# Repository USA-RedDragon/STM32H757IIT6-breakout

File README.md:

# STM32H757IIT6 Breakout

This board is aimed to evaluate the ST Microelectronics STM32H757IIT6 for use in an ultra-wideband SDR radio.

## Current Status

Not useful. This board should be usable for powering the STM, but features some unconnected pin headers.

## BOM

As of writing, the BOM comes out to $131.83 USD.

Octopart: https://octopart.com/bom-tool/58tXZVEL

## Size

TBD

## Images

All images below are of a pre-production board

### Top Right Angled View

### Top

## Bottom

## Usage

TODO

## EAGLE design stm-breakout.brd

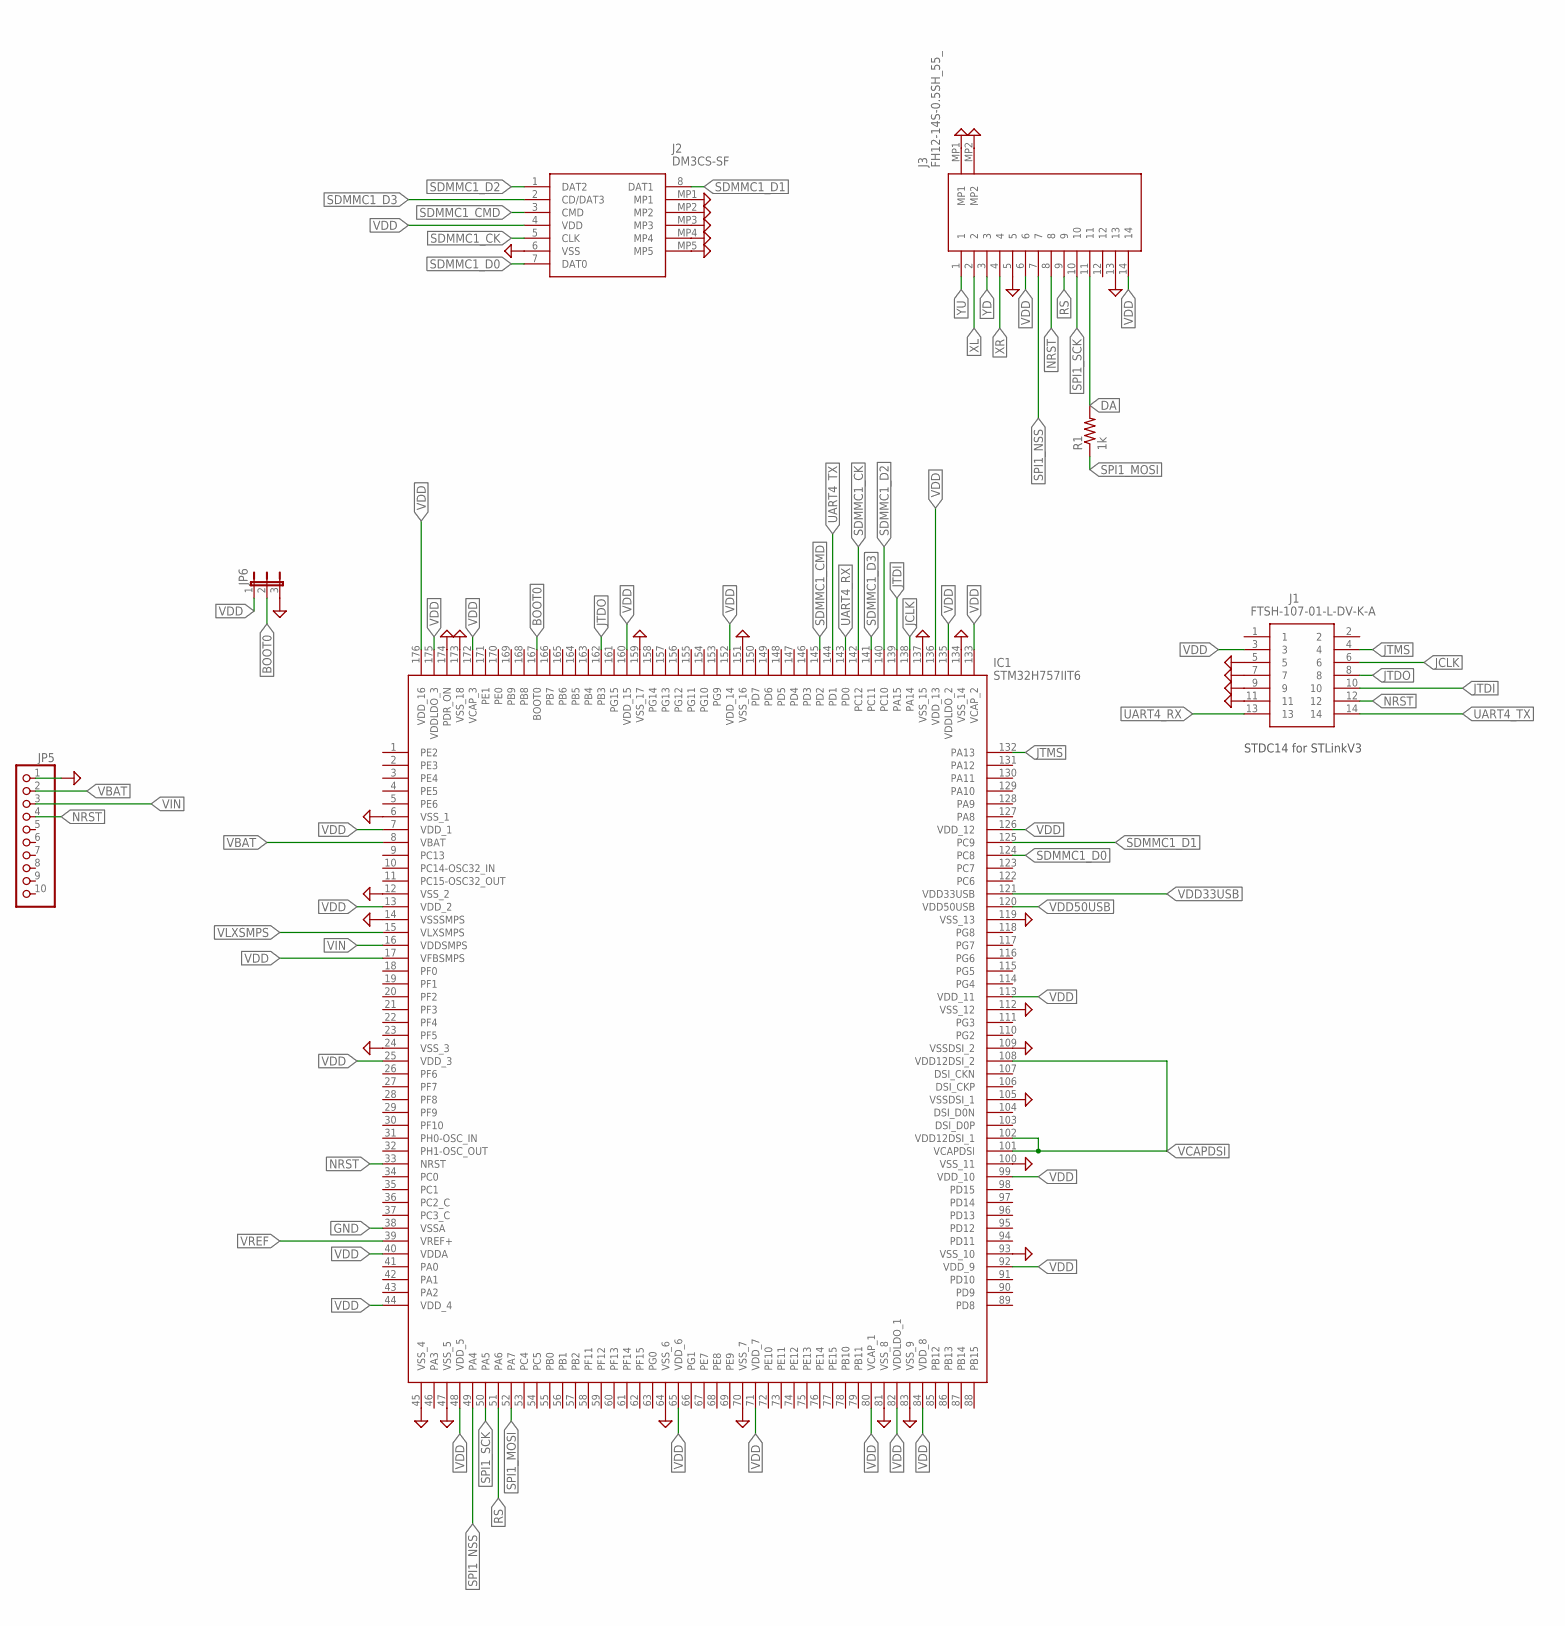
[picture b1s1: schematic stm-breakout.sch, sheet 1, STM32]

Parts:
IC1: STM32H757IIT6; QFP50P2600X2600X160-176N
J1: FTSH-107-01-L-DV-K-A; FTSH-107-XX-YYY-DV-K-A
J2: DM3CS-SF; DM3CSSF
J3: FH12-14S-0.5SH_55_; FH1214S05SH55
JP5: PINHD-1X10; 1X10
JP6: JP2
R1: 1k; R0402

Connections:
BOOT0: IC1.167 (BOOT0), JP6.2
DA: J3.11, R1.2
GND: IC1.6 (VSS_1), IC1.12 (VSS_2), IC1.14 (VSSSMPS), IC1.24 (VSS_3), IC1.38 (VSSA), IC1.45 (VSS_4), IC1.47 (VSS_5), IC1.64 (VSS_6), IC1.70 (VSS_7), IC1.81 (VSS_8), IC1.83 (VSS_9), IC1.93 (VSS_10), IC1.100 (VSS_11), IC1.105 (VSSDSI_1), IC1.109 (VSSDSI_2), IC1.112 (VSS_12), IC1.119 (VSS_13), IC1.134 (VSS_14), IC1.137 (VSS_15), IC1.151 (VSS_16), IC1.159 (VSS_17), IC1.173 (VSS_18), IC1.174 (PDR_ON), J1.5, J1.7, J1.9, J1.11, J2.6 (VSS), J2.MP1, J2.MP2, J2.MP3, J2.MP4, J2.MP5, J3.5, J3.13, J3.MP1, J3.MP2, JP5.1, JP6.3; also elsewhere on the board
JCLK: IC1.138 (PA14), J1.6
JTDI: IC1.139 (PA15), J1.10
JTDO: IC1.162 (PB3), J1.8
JTMS: IC1.132 (PA13), J1.4
NRST: IC1.33 (NRST), J1.12, J3.8, JP5.4; also elsewhere on the board
RS: IC1.51 (PA6), J3.9
SDMMC1_CK: IC1.142 (PC12), J2.5 (CLK)
SDMMC1_CMD: IC1.145 (PD2), J2.3 (CMD)
SDMMC1_D0: IC1.124 (PC8), J2.7 (DAT0)
SDMMC1_D1: IC1.125 (PC9), J2.8 (DAT1)
SDMMC1_D2: IC1.140 (PC10), J2.1 (DAT2)
SDMMC1_D3: IC1.141 (PC11), J2.2 (CD/DAT3)
SPI1_MOSI: IC1.52 (PA7), R1.1
SPI1_NSS: IC1.49 (PA4), J3.7
SPI1_SCK: IC1.50 (PA5), J3.10
UART4_RX: IC1.143 (PD0), J1.13
UART4_TX: IC1.144 (PD1), J1.14
VBAT: IC1.8 (VBAT), JP5.2
VCAPDSI: IC1.101 (VCAPDSI), IC1.102 (VDD12DSI_1), IC1.108 (VDD12DSI_2); also elsewhere on the board
VDD: IC1.7 (VDD_1), IC1.13 (VDD_2), IC1.17 (VFBSMPS), IC1.25 (VDD_3), IC1.40 (VDDA), IC1.44 (VDD_4), IC1.48 (VDD_5), IC1.65 (VDD_6), IC1.71 (VDD_7), IC1.80 (VCAP_1), IC1.82 (VDDLDO_1), IC1.84 (VDD_8), IC1.92 (VDD_9), IC1.99 (VDD_10), IC1.113 (VDD_11), IC1.126 (VDD_12), IC1.133 (VCAP_2), IC1.135 (VDDLDO_2), IC1.136 (VDD_13), IC1.152 (VDD_14), IC1.160 (VDD_15), IC1.172 (VCAP_3), IC1.175 (VDDLDO_3), IC1.176 (VDD_16), J1.3, J2.4 (VDD), J3.6, J3.14, JP6.1; also elsewhere on the board
VDD33USB: IC1.121 (VDD33USB); also elsewhere on the board
VDD50USB: IC1.120 (VDD50USB); also elsewhere on the board
VIN: IC1.16 (VDDSMPS), JP5.3; also elsewhere on the board
VLXSMPS: IC1.15 (VLXSMPS); also elsewhere on the board
VREF: IC1.39 (VREF+); also elsewhere on the board
XL: J3.2
XR: J3.4
YD: J3.3
YU: J3.1

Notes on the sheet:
STDC14 for STLinkV3

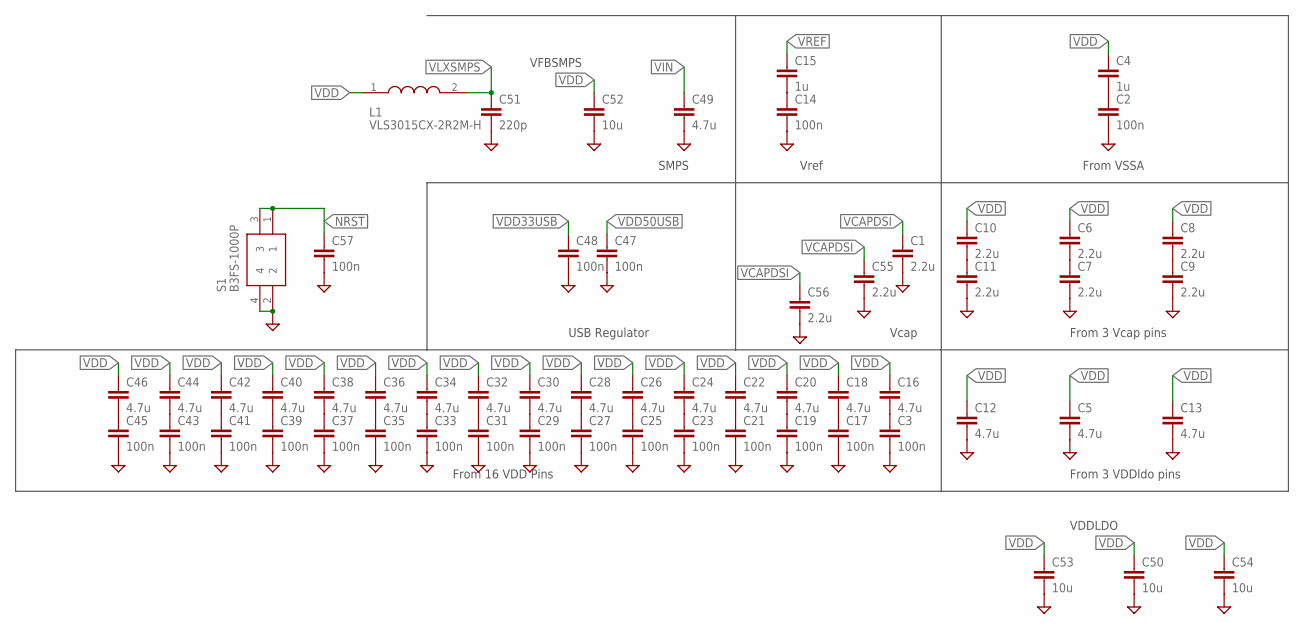
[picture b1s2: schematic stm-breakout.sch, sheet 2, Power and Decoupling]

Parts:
C1, C6, C7, C8, C9, C10, C11, C55, C56: 2.2u; C0603
C2, C3, C14, C17, C19, C21, C23, C25, C27, C29, C31, C33, C35, C37, C39, C41, C43, C45, C47, C48, C57: 100n; C0402
C4, C15: 1u; C0603
C5, C12, C13, C16, C18, C20, C22, C24, C26, C28, C30, C32, C34, C36, C38, C40, C42, C44, C46, C49: 4.7u; C0603
C50, C52, C53, C54: 10u; C0603
C51: 220p; C0402
L1: VLS3015CX-2R2M-H; VLS3015
S1: B3FS-1000P

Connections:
GND: C1.2, C2.2, C3.2, C5.2, C7.2, C9.2, C11.2, C12.2, C13.2, C14.2, C17.2, C19.2, C21.2, C23.2, C25.2, C27.2, C29.2, C31.2, C33.2, C35.2, C37.2, C39.2, C41.2, C43.2, C45.2, C47.2, C48.2, C49.2, C50.2, C51.2, C52.2, C53.2, C54.2, C55.2, C56.2, C57.2, S1.2, S1.4; also elsewhere on the board
unnamed: C2.1, C4.2
unnamed: C6.2, C7.1
unnamed: C8.2, C9.1
unnamed: C10.2, C11.1
NRST: C57.1, S1.1, S1.3; also elsewhere on the board
VCAPDSI: C1.1, C55.1, C56.1; also elsewhere on the board
VDD: C4.1, C5.1, C6.1, C8.1, C10.1, C12.1, C13.1, C16.1, C18.1, C20.1, C22.1, C24.1, C26.1, C28.1, C30.1, C32.1, C34.1, C36.1, C38.1, C40.1, C42.1, C44.1, C46.1, C50.1, C52.1, C53.1, C54.1, L1.1; also elsewhere on the board
VDD33USB: C48.1; also elsewhere on the board
VDD50USB: C47.1; also elsewhere on the board
VIN: C49.1; also elsewhere on the board
VLXSMPS: C51.1, L1.2; also elsewhere on the board
VREF: C15.1; also elsewhere on the board
VREFNF: C14.1, C15.2
VREFNF1: C3.1, C16.2
VREFNF2: C17.1, C18.2
VREFNF3: C19.1, C20.2
VREFNF4: C21.1, C22.2
VREFNF5: C23.1, C24.2
VREFNF6: C25.1, C26.2
VREFNF7: C27.1, C28.2
VREFNF8: C29.1, C30.2
VREFNF9: C31.1, C32.2
VREFNF10: C33.1, C34.2
VREFNF11: C35.1, C36.2
VREFNF12: C37.1, C38.2
VREFNF13: C39.1, C40.2
VREFNF14: C41.1, C42.2
VREFNF15: C43.1, C44.2
VREFNF16: C45.1, C46.2

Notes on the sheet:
From VSSA
From 3 Vcap pins
From 3 VDDldo pins
From 16 VDD Pins
Vcap
Vref
USB Regulator
SMPS
VFBSMPS
VDDLDO

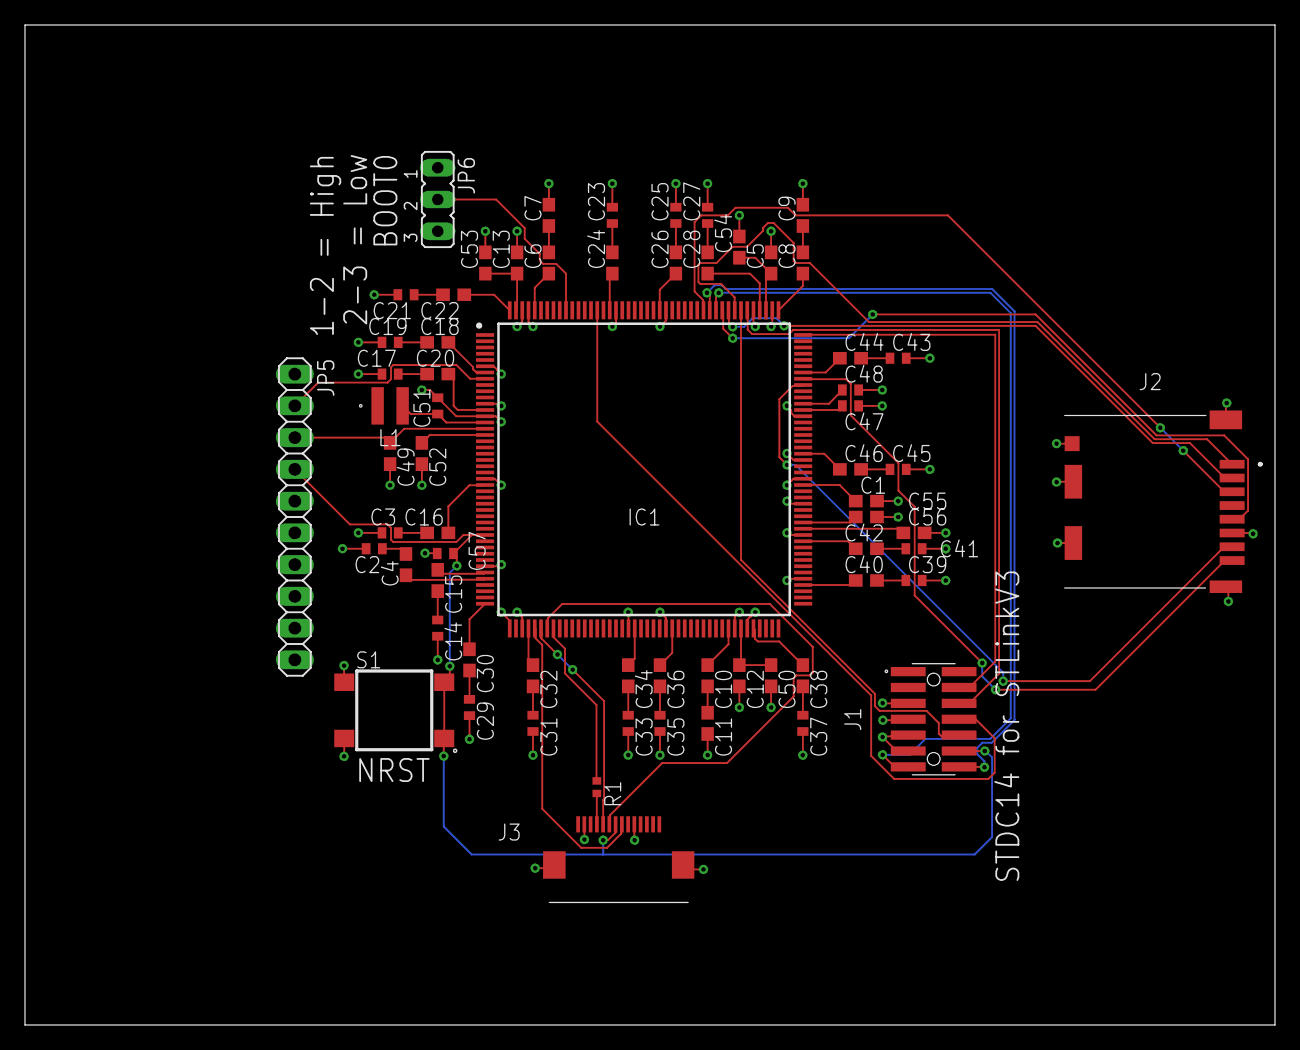
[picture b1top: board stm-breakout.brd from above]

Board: 2 copper layers, 100.0 x 80.0 mm, 66 parts (0 on the bottom side), 49 nets.

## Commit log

2022-09-02 Add in power filtering and SMPS functionality
2022-09-02 Add images
2022-09-03 Add nrst switch, sdcard, TFT display connector, and jtag
